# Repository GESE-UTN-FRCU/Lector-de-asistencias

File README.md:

# Proyecto lector de asistencias

Este proyecto es un lector de tarjetas RFID que envia el codigo leido junto a una fecha y hora y la IP del dispositivo. Este sistema fue diseñado para implementarse en la UTN-FRCU.

## Componentes utilizados:
+Arduino nano
+DS3231
+ENC28J60
+RC522
+LCD 16x2

## Integrantes:

+Alfaro Diego

+Chichi Manuel

+Garcia Alejo

+Venditti Juan Pablo

## Profesor:

+Hoet Leonardo

### TO DO (segun importancia)

+Cambiar headers a librerias bien planteadas.

+Chequear overflow del millis o hacer un reset por mes.

+Agregar seguridad a el dispositivo.

+

### Secciones:

+LectorUTN      - Contiene el codigo arduino en C del lector (este se sube en .

+Diagramas PCB  - Contiene los diagramas de las conexiones fisicas del lector.

+Pagina web     - Contiene la pagina web a la que enviara datos el lector.

# MANUAL DE USUARIO

## Configuración del dispositivo

Para el funcionamiento del sistema, primero es necesario establecer su configuración inicial. En esta, se tendrá que asignar al dispositivo un gateway (dirección IP del modem), una dirección ip del dispositivo, una dirección ip del servidor, una máscara de subred y un puerto (80 por defecto). 
Para realizar esta configuración se debe ingresar al modo de configuración del dispositivo. Para entrar al modo de configuración el usuario tiene que presionar el botón correspondiente al iniciar el sistema, cuando la pantalla está vacía.
Una vez que el dispositivo se encuentra en modo de configuración, es necesario acceder a través de un navegador web a la ip por defecto del modo de configuración “192.168.8.152”, y asi podrá acceder a la siguiente página web.

Una vez dentro de la página web, se deberá completar los campos correspondientes y oprimir el botón “Guardar”. Posteriormente, el sistema se reiniciará y los valores ingresados a través de la página de configuración quedarán asignados.
ADVERTENCIA: Una vez pasado el dispositivo a modo configuración, todas las lecturas guardadas en memoria serán eliminadas.

## Modo lector de tarjetas

Para llevar a cabo el proceso de lectura de tarjetas, solo es necesario pasar la tarjeta a corta distancia por delante del dispositivo.

Es necesario tener en cuenta ciertos criterios para que el dispositivo se encuentre disponible para la lectura de tarjetas:
El dispositivo tiene que haber sido previamente configurado (Ver sección “Configuración del dispositivo” para más información).
El dispositivo se debe encontrar disponible para leer tarjetas, mostrando en su pantalla el mensaje “Pasar tarjeta”.
El dispositivo debe estar fuera de horario de envío de datos, en este caso se mostrará en su pantalla el mensaje “No disponible”.
El dispositivo no se debe encontrar en modo configuración, mostrando en pantalla “Modo config.”
El dispositivo actualizará su fecha y hora realizando una petición al servidor cada dos horas. Cuando esto sucede, se mostrará un mensaje “Actualizando...” en la pantalla.

## Modo envío de datos

Este modo consiste en el envío al servidor de los datos recolectados en las últimas lecturas y que no hayan sido enviados y confirmados por el servidor previamente.
Este modo se encuentra disponible en el horario entre las 2 a.m. y las 4 a.m. a lo largo de todos los días del año.

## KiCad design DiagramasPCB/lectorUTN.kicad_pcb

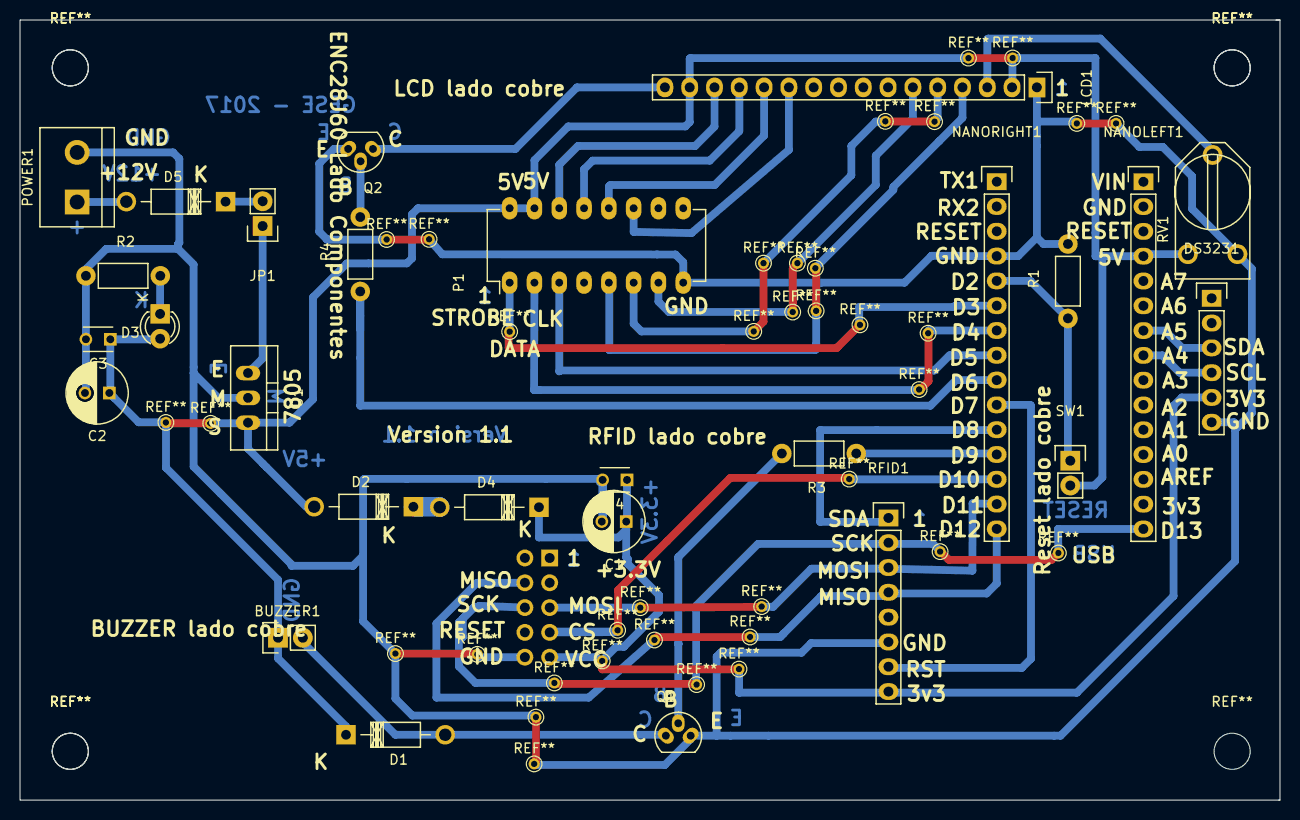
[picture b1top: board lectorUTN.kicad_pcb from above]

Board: 2 copper layers, 129.0 x 79.9 mm, 28 parts (1 on the bottom side), 34 nets.

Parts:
BUZZER1: CONNECTOR_BUZZER; Pin_Header_Straight_1x02
C1, C2: 10x16; C_Radial_D6.3_L11.2_P2.5
C3, C4: 0.1; C_Disc_D3_P2.5
D1, D2, D4, D5: 1N4007; Diode_DO-41_SOD81_Horizontal_RM10
D3: LED_3mm; LED-3MM
DS3231: CLOCK; Pin_Header_Straight_1x06
ENC28J60: ETHERNET; Pin_Header_Straight_2x05
JP1: JUMPER; Pin_Header_Straight_1x02
LCD1: DISPLAY_LCD; Pin_Header_Straight_1x16
NANOLEFT1: NANO_LEFT_CONN; Pin_Header_Straight_1x15
NANORIGHT1: NANO_RIGHT_CONN; Pin_Header_Straight_1x15
P1: CD4094; DIP-16_W7.62mm_LongPads
POWER1: +12; bornier2
Q1, Q2: BC337; TO-92_Molded_Narrow_Oval
R1, R3: 1k; Resistor_Horizontal_RM7mm
R2: 220; Resistor_Horizontal_RM7mm
R4: 1K; Resistor_Horizontal_RM7mm
RFID1: RFID; Pin_Header_Straight_1x08
RV1: 1K; RV2X4
SW1: RESET; Pin_Header_Straight_1x02
U1: 7805; TO-220_Neutral123_Vertical

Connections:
unnamed: BUZZER1.1, C2.1, C3.1, D1.1, D2.2, D3.2, LCD1.2, LCD1.15, NANOLEFT1.4, P1.15, P1.16, RV1.1, SW1.2, U1.3
unnamed: BUZZER1.2, D1.2, Q1.1
unnamed: C1.1, C4.1, D4.1, DS3231.5, ENC28J60.9, RFID1.8
unnamed: C1.2, C2.2, C3.2, C4.2, DS3231.6, ENC28J60.10, LCD1.1, NANORIGHT1.4, P1.8, POWER1.2, Q1.3, R1.2, R2.1, RFID1.6, RV1.3, U1.2
unnamed: D2.1, D4.2
unnamed: D3.1, R2.2
unnamed: D5.1, JP1.2
unnamed: D5.2, POWER1.1
unnamed: DS3231.3, NANOLEFT1.7
unnamed: DS3231.4, NANOLEFT1.8
unnamed: ENC28J60.4, NANORIGHT1.15, RFID1.4
unnamed: ENC28J60.5, NANORIGHT1.14, RFID1.3
unnamed: ENC28J60.6, NANOLEFT1.15, RFID1.2
unnamed: ENC28J60.7, NANORIGHT1.13
unnamed: JP1.1, U1.1
unnamed: LCD1.3, RV1.2
unnamed: LCD1.4, P1.5
unnamed: LCD1.5, P1.6
unnamed: LCD1.6, P1.7, Q2.3
unnamed: LCD1.11, P1.11
unnamed: LCD1.12, P1.12
unnamed: LCD1.13, P1.13
unnamed: LCD1.14, P1.14
unnamed: LCD1.16, Q2.1
unnamed: NANORIGHT1.5, R1.1, SW1.1
unnamed: NANORIGHT1.6, P1.1
unnamed: NANORIGHT1.7, P1.2
unnamed: NANORIGHT1.8, P1.3
unnamed: NANORIGHT1.9, R4.1
unnamed: NANORIGHT1.10, RFID1.7
unnamed: NANORIGHT1.11, RFID1.1
unnamed: NANORIGHT1.12, R3.1
unnamed: Q1.2, R3.2
unnamed: Q2.2, R4.2

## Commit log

2017-08-29 Diagramas PCB
2017-08-29 Descripcion agregada
2017-08-29 Pagina web subida
2017-10-13 DiagramasPCB actualizados
